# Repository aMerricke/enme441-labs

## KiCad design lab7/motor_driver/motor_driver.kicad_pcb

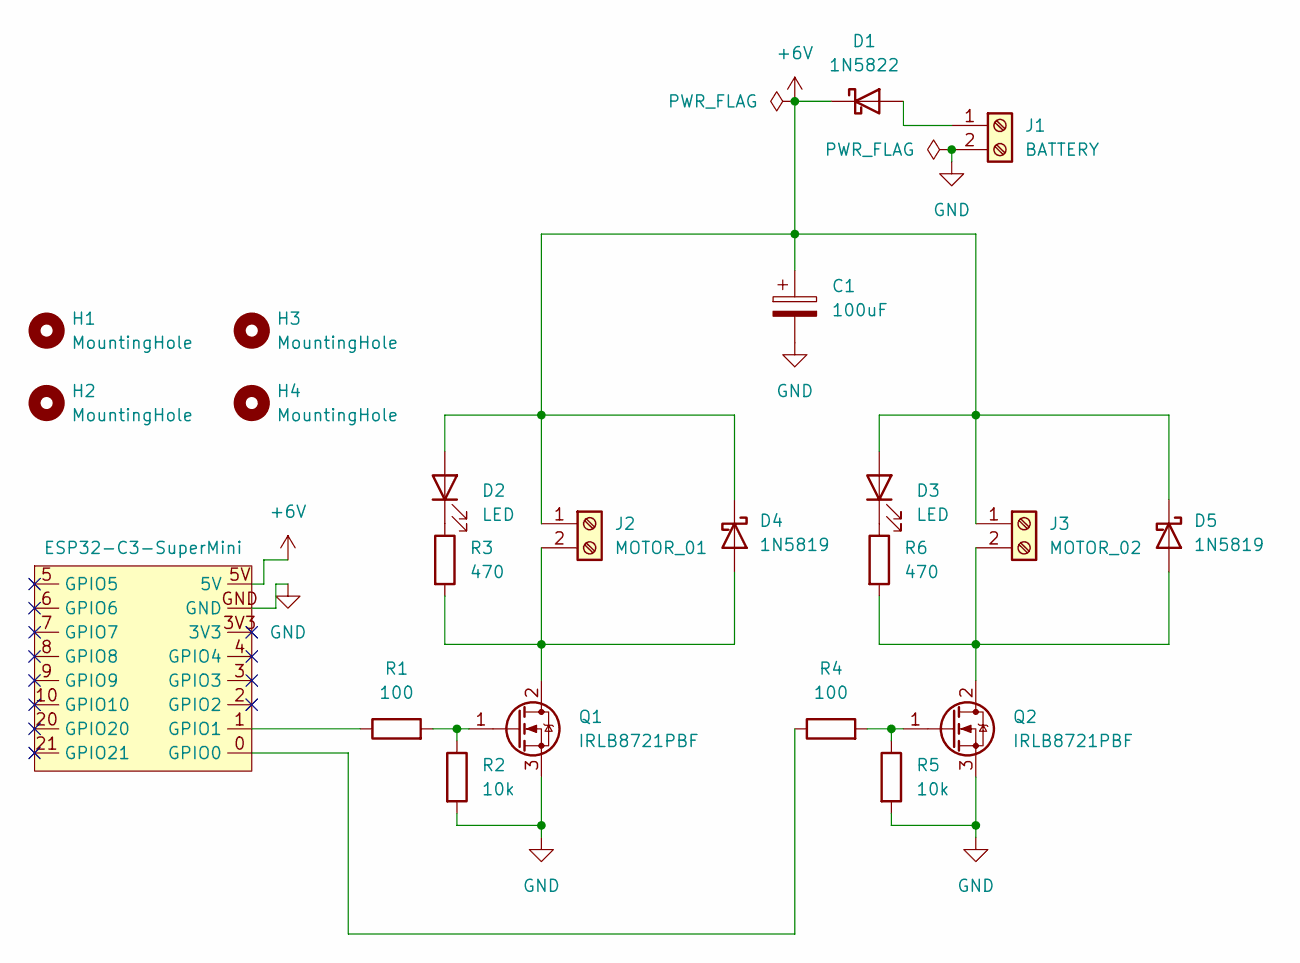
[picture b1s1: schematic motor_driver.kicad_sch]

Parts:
C1: 100uF; CP_Radial_D6.3mm_P2.50mm
D1: 1N5822; D_DO-201AD_P15.24mm_Horizontal
D2, D3: LED; LED_D5.0mm
D4, D5: 1N5819; D_DO-41_SOD81_P10.16mm_Horizontal
H1, H2, H3, H4: MountingHole; MountingHole_3.2mm_M3
J1: BATTERY; TerminalBlock_Phoenix_MKDS-1,5-2_1x02_P5.00mm_Horizontal
J2: MOTOR_01; TerminalBlock_Phoenix_MKDS-1,5-2_1x02_P5.00mm_Horizontal
J3: MOTOR_02; TerminalBlock_Phoenix_MKDS-1,5-2_1x02_P5.00mm_Horizontal
Q1, Q2: IRLB8721PBF; TO-220-3_Vertical
R1, R4: 100; R_Axial_DIN0207_L6.3mm_D2.5mm_P10.16mm_Horizontal
R2, R5: 10k; R_Axial_DIN0207_L6.3mm_D2.5mm_P10.16mm_Horizontal
R3, R6: 470; R_Axial_DIN0207_L6.3mm_D2.5mm_P10.16mm_Horizontal
U1: ESP32-C3-SuperMini

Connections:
+6V: C1.1, D1.1 (K), D2.2 (A), D3.2 (A), D4.1 (K), D5.1 (K), J2.1, J3.1, U1.5V
GND: C1.2, J1.2, Q1.3 (S), Q2.3 (S), R2.2, R5.2, U1.GND
unnamed: D1.2 (A), J1.1
unnamed: D2.1 (K), R3.1
unnamed: D3.1 (K), R6.1
unnamed: D4.2 (A), J2.2, Q1.2 (D), R3.2
unnamed: D5.2 (A), J3.2, Q2.2 (D), R6.2
unnamed: Q1.1 (G), R1.2, R2.1
unnamed: Q2.1 (G), R4.2, R5.1
unnamed: R4.1, U1.0 (GPIO0)
unnamed: R1.1, U1.1 (GPIO1)

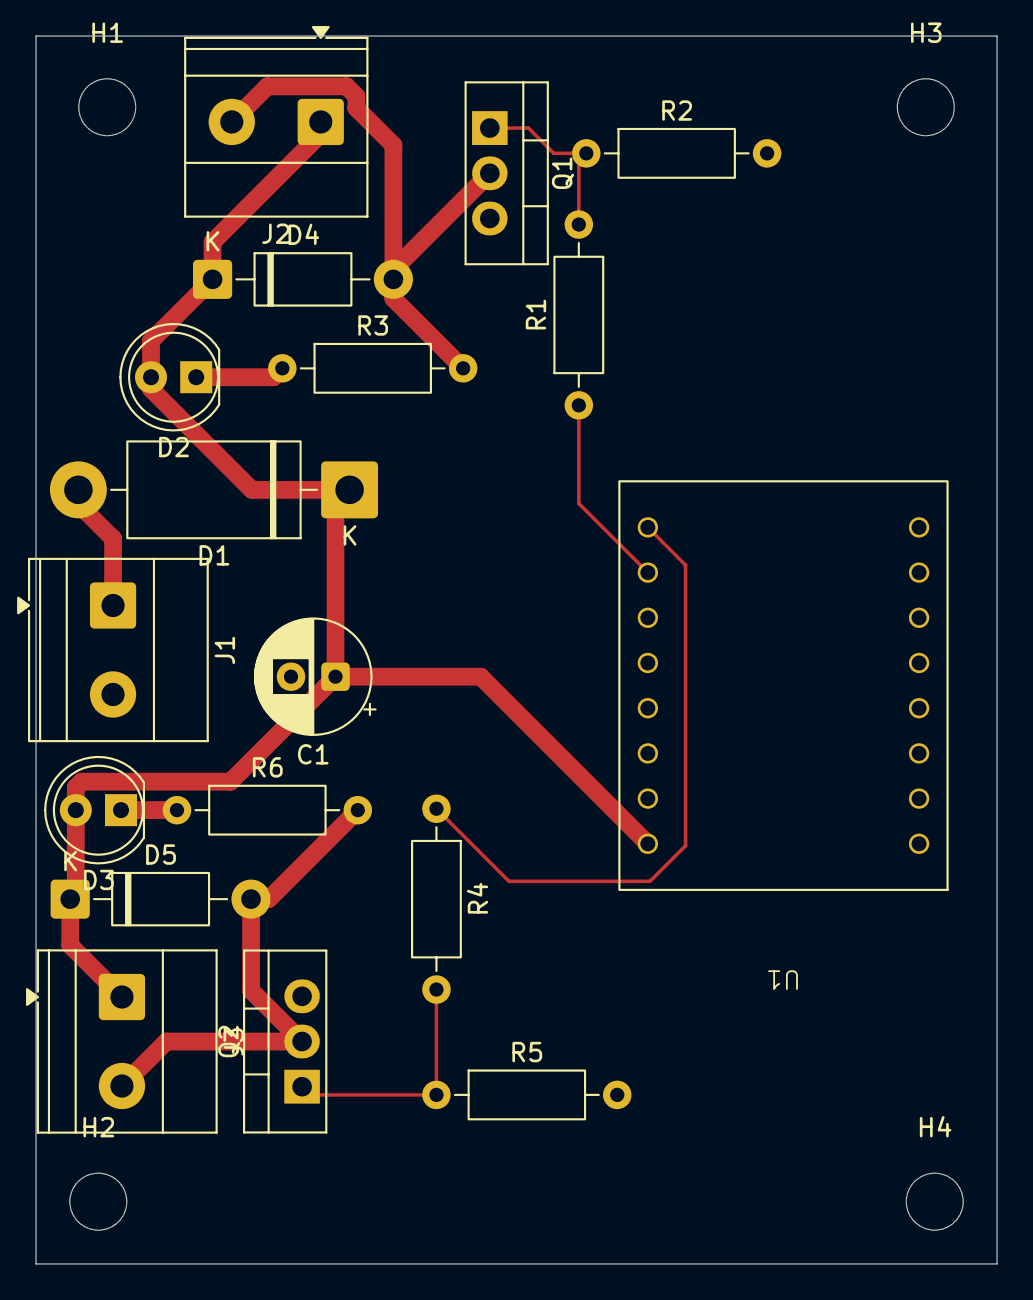
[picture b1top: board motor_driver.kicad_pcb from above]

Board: 2 copper layers, 54.0 x 69.0 mm, 22 parts (0 on the bottom side), 11 nets.
